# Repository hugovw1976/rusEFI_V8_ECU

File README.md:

# rusEFI_V8_ECU

- 8x 3A low-side drivers
- 4x 10A low_side drivers
- 8x 5v ignition or general purpose outputs (or 4 igniters/ 4general purpose otputs)
- One H-bridge for electronic throttle
- 10x Analog voltage inputs
- 4x Analog temperature (5v pullup) inputs
- 2x VR crank/cam/vehicle speed inputs
- 6x hall cam/crank or digital input (-2 if VR sensors used)
- Base on proteus board (intended for use with proteus firmware microcontroller, pin matched to correspond output)

rusEFI project: https://github.com/rusefi/rusefi
Proteus project: https://github.com/mck1117/proteus

Please do not use the gerber files, the board is not tested yet!
P&P file not tested on JLC PCB (Board is hand soldering)

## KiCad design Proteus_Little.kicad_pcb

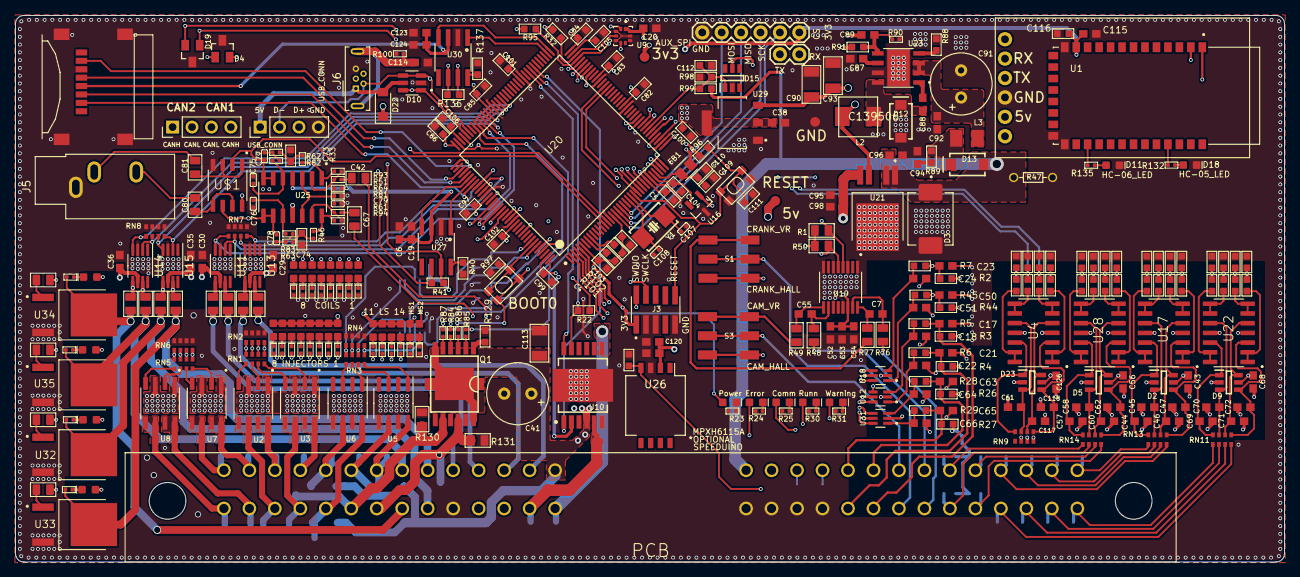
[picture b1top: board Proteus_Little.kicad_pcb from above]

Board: 4 copper layers, 166.0 x 71.5 mm, 394 parts (0 on the bottom side), 288 nets.

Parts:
C1, C2, C3, C8, C9, C10, C11, C12, C13, C14, C15, C16, C25, C26, C27, C28, C31, C32, C33, C34, C39, C40, C48, C49, C54, C87: 10nF; 0603
C4, C5, C82, C83, C84, C85, C86, C97, C99, C104, C109, C111: 10nf; C0603
C6, C53, C92, C95, C96, C119, C120, C123: 1.0uF; 0603
C7, C17, C18, C21, C22, C23, C24, C50, C51, C55, C63, C64, C65, C66: 1nF; 0603
C19, C20, C29, C30, C35, C36, C37, C44, C45, C46, C47, C52, C57, C58, C60, C61, C62, C69, C70, C71, C72, C88, C115, C117, C118, C124, C125: 100nF; 0603
C38, C94: 4.7uF; 0603
C41, C91: 56uF; E3,5-8
C42, C67: 3.3nf; C0805
C43, C56, C68, C126: 33nF; 0603
C73, C74: 680pf; C0603
C75, C76: 47PF; C0402
C77, C78: 330PF 50V; C0402
C79: 10nf; C0402
C80, C81: 10uf; C0805
C89: 270PF; 0603
C90, C93, C113: 10uf; C1206
C98: 22uf; 0603
C100, C101, C102, C103: 4.7uf; C0603
C105, C106: 2.2uf; C0603
C107, C108: 33pf; C0402
C110: 4.7uF; C0603
C112, C116: 1uf; C0603
C114: 100nf; 0603
D1: BLUE; LED-0603
D2, D5, D9, D15, D23: SRV05-4.TCT; SOT95P280X145-6N
D3: SM15T33CA; DIOM7959X262N
D4, D19: PESD1CAN; SOT23
D6, D7: GREEN; LED-0603
D8, D11, D18, D27, D28, D29, D30, D31, D32, D33, D34, D35, D36, D37, D38, D39, D40, D41, D42, D43, D44, D45, D46, D47, D48, D49, D50, D51, D52: RED; LED-0603
D10: USBLC6-2SC6; SOT95P280X145-6N
D12, D13: C8678; SMA-DIODE
D14: Yellow; LED-0603
D16, D17, D20, D21: MBR0520LT1G; SOD-123FL
D22: MBR0520LT1G; SODFL3718X115
FB1: FERRITE_BEAD; BEADC2012X105N
J1, J9: Conn_01x04_Female; PinHeader_1x04_P2.54mm_Vertical
J2: 47219-2001; MOLEX_47219-2001
J3: 62131021021
J4: CONN_06NO_SILK_NO_POP; 1X06_NO_SILK
J5: AudioJack3; Jack_3.5mm_CUI_SJ1-3533NG_Horizontal
J6: USB_B_Micro; USB_Micro-B_Wuerth_614105150721_Vertical
J7: CONN_02; 1X02
J8: CONN_06SILK_FEMALE_PTH; 1X06
L2: 10U; 0503
L3: 2.2U; L3225M
Q1: BTS5215L; PG-DSO-12-9
R1, R48, R49, R50, R76, R77: 10K; R0805
R2, R3, R4, R26, R27, R32, R44, R95: 2.2K; R0603
R5, R6, R7, R28, R29, R45: 3.3K; R0603
R8, R9, R10, R11, R12, R13, R14, R15: 100R; R0805
R16, R17, R34: 2.7K; R0603
R18, R19, R20, R21, R22, R40, R53, R54, R55, R56, R65, R67, R78, R79, R88, R96, R97, R98, R101, R102, R137, R138, R139, R140, R141, R147, R148, R149, R150: 10K; R0603
R23, R24, R25, R30, R31, R103, R104, R105, R106, R107, R108, R109, R110, R111, R112, R113, R114, R115, R116, R117, R118, R119, R120, R121, R122, R123, R124, R125, R126, R127, R128, R132, R135: 330R; R0402
R33, R46, R90: 12K; R0402
R35, R36, R37, R38, R57, R58, R59, R60, R68, R69, R70, R71, R143, R144, R145, R146: 5.6K; R0603
R39, R42, R43, R52, R66, R72, R73, R74, R75, R92, R133: 470K; R0603
R41, R136: 120R; R0603
R47: B72530T6170K062; R-5
R51, R61, R62, R63, R100: 100K; R0402
R64, R81: 22K; R0402
R80: 2.7k; R0603
R82, R83: 33K; R0402
R84, R85: 10K; R0402
R86, R87: 15K; R0402
R89: 1R; R0603
R91: 68K; R0603
R93, R94: 470K; R0402
R99: 82k; R0603
R129: 150R; R0603
R130, R131: 4.7K; R0805
R1020, R1021, R1022: 330R; R0805
R1023: 330r; R0805
RN1, RN2, RN3, RN4, RN5, RN6, RN7, RN8: 1K; 0603-ARC
RN9, RN11, RN13, RN14: 10K; 0603-ARC
S1, S3: JS202011SCQN; SW_JS202011SCQN
SW1, SW2: SPST_TACT-KMR2; KMR2
TP1, TP2, TP3: TEST-POINT3X5; PAD.03X.05
U1: HC-05; XCVR_HC-05
U2, U3, U7, U8: VNS3NV04DP-E; SOIC127P600X175-8N
U4, U17, U22, U25, U28: MCP6004-E_SL; SOIC127P600X175-14N
U5, U6: VNLD5090TR-E; SOIC-8_3.9x4.9mm_P1.27mm
U9: LPS25HBTR; PQFN60P250X250X80-10N
U10: TLE9201SG; SOP100P1030X260-13N
U11, U13, U14, U15: MIC4427; MSOP-8_3x3mm_P0.65mm
U12, U18, U31: 74HC2G17; SOP65P210X110-6N
U16: REF3033AIDBZR; SOT95P237X112-3N
U19: MAX9926UAEE+; SOP63P602X175-16N
U20: STM32F407ZGT6; STMICROELECTRONICS_STM32F429ZGT6_2
U21: TLE4251DATMA1; TO114P998X235-5
U23: LMR14020SDDAR; VREG_LM5017MR_NOPB
U26: MPXAZ6115A; Freescale_98ARH99066A
U27, U30: VD230; SO08
U29: AMS1117-3.3; SOT229P700X180-4N
U32, U33, U34, U35: ISL9V3040D3STV; TO229P990X238-4N
U36: 74HC125DB,112; SOP65P775X265-14N
U$1: MCP6002-E_SN; SOIC127P599X175-8N
U$3: 211PL562L0011; 211PL562L0011_2
Y1: CRYSTAL_NX5032GA; CRYSTAL_2-SMD-5X3

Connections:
+3V3: C4.1, C5.1, C6.1, C19.1, C20.1, C38.2, C82.1, C83.1, C84.1, C85.1, C86.1, C97.1, C99.1, C100.1, C101.1, C102.1, C103.1, C115.2, C116.1, C123.1, C124.1, D6.A, FB1.2, J2.4, J3.1, J8.6, R1.2, R22.2, R32.1, R50.2, R64.2, R86.1, R87.1, R95.2, R96.1, R101.2, R102.2, SW2.1, SW2.3, TP2.P$1, U1.12, U9.1, U9.6, U9.10, U10.2, U20.6, U20.17, U20.30, U20.39, U20.52, U20.62, U20.72, U20.84, U20.95, U20.108, U20.121, U20.131, U20.143, U20.144, U25.4, U27.3, U29.2, U29.4, U30.3
+5V: C29.1, C30.1, C35.1, C36.1, C43.1, C52.2, C53.1, C54.2, C56.1, C68.1, C89.2, C90.1, C93.1, C119.1, C120.1, C125.2, C126.1, D2.5, D5.5, D9.5, D15.5, D22.1, D23.5, D27.A, D28.A, D29.A, D30.A, D31.A, D32.A, D33.A, D34.A, D35.A, D36.A, D37.A, D38.A, D49.A, D50.A, D51.A, D52.A, J4.2, L2.P$2, R91.2, TP1.P$1, U4.4, U11.6, U12.5, U13.6, U14.6, U15.6, U16.1, U17.4, U18.5, U19.14, U21.4, U22.4, U26.2, U28.4, U29.3, U31.5, U36.14, U$1.8
/5V_SENSORS: C37.1, C95.2, C98.2, R2.1, R3.1, R4.2, R16.2, R17.2, R26.1, R27.2, R34.2, R44.1, R80.2, U21.5, U$3.P55
/12 VOLT DIVIDER/12V_DIVIDED: C112.2, D15.1, R98.2, R99.1, U20.43
/12V: C96.2, D3.1, D13.A, R47.1, R99.2, U21.1, U21.2, U$3.P56
/12V_MR: C41.+, C113.1, D16.C, D17.C, D20.C, D21.C, Q1.6, Q1.12, Q1.EXP, U10.4, U$3.P15
/ANALOG1: R72.2, RN11.8, U$3.P39
/ANALOG1/ANALOG1_MCU: R21.2, R68.2, U20.26
/ANALOG1/ANALOG2_MCU: R20.2, R69.2, U20.27
/ANALOG1/ANALOG3_MCU: R19.2, R70.2, U20.28
/ANALOG1/ANALOG4_MCU: R18.2, R71.2, U20.29
/ANALOG2: R73.2, RN11.7, U$3.P40
/ANALOG2/ANALOG5_MCU: R35.2, R56.2, U20.34
/ANALOG2/ANALOG6_MCU: R36.2, R55.2, U20.35
/ANALOG2/ANALOG7_MCU: R37.2, R54.2, U20.36
/ANALOG2/ANALOG8_MCU: R38.2, R53.2, U20.37
/ANALOG3: R74.2, RN11.6, U$3.P41
/ANALOG3/ANALOG9_MCU: R143.2, R150.2, U20.40
/ANALOG3/ANALOG10_MCU: R144.2, R149.2, U20.41
/ANALOG3/ANALOG11_MCU: R145.2, R148.2, U20.42
/ANALOG4: R75.2, RN11.5, U$3.P42
/ANALOG5: R39.2, RN13.8, U$3.P46
/ANALOG6: R42.2, RN13.7, U$3.P45
/ANALOG7: R43.2, RN13.6, U$3.P44
/ANALOG8: R52.2, RN13.5, U$3.P43
/ANALOG9: R66.2, RN9.8, U26.4
/ANALOG10: R92.2, RN9.7, U$3.P53
/ANALOG11: R133.2, RN9.6, U$3.P54
/ANALOG_T1: R17.1, RN14.5, U$3.P48
/ANALOG_T2: R16.1, RN14.6, U$3.P37
/ANALOG_T3: R80.1, RN14.7, U$3.P47
/ANALOG_T4: R34.1, RN14.8, U$3.P38
/ANALOG_T/ANALOG_T1_MCU: R60.2, R65.2, U20.44
/ANALOG_T/ANALOG_T2_MCU: R59.2, R67.2, U20.45
/ANALOG_T/ANALOG_T3_MCU: R58.2, R78.2, U20.46
/ANALOG_T/ANALOG_T4_MCU: R57.2, R79.2, U20.47
/AUX_SPI_CS: J8.5, U20.18
/AUX_SPI_MISO: J8.3, U20.20
/AUX_SPI_MOSI: J8.2, U20.21
/AUX_SPI_SCK: J8.4, U20.19
/BARO/BARO_SCL: R95.1, U9.2, U20.69
/BARO/BARO_SDA: R32.2, U9.4, U20.70
/CAM+: S3.2, S3.5, U$3.P50
/CAM-: R48.2, U$3.P49
/CAN1H: D4.2, J1.4, R41.2, U27.7
/CAN1L: D4.1, J1.3, R41.1, U27.6
/CAN2H: D19.2, J1.1, R136.2, U30.7
/CAN2L: D19.1, J1.2, R136.1, U30.6
/CAN/CAN1_RX: U20.114, U27.4
/CAN/CAN1_TX: U20.115, U27.1
/CAN/CAN2_RX: U20.73, U30.4
/CAN/CAN2_TX: U20.74, U30.1
/COIL1: C28.1, D42.A, R11.2, U$3.P17
/COIL2: C27.1, D43.A, R10.2, U$3.P16
/COIL3: C25.1, D44.A, R8.2, U$3.P18
/COIL4: C26.1, D45.A, R9.2, U$3.P19
/COIL5: C33.1, D46.A, R14.2, R125.2, U33.4, U$3.P20
/COIL6: C34.1, D47.A, R15.2, R126.2, U32.4, U$3.P9
/COIL7: C31.1, D48.A, R12.2, R127.2, U35.4, U$3.P21
/COIL8: C32.1, D41.A, R13.2, R128.2, U34.4, U$3.P8
/CRANK+: S1.2, S1.5, U$3.P35
/CRANK-: R76.2, U$3.P36
/ETB/DIR: U10.1, U20.79
/ETB/DIS: R22.1, U10.11, U20.80
/ETB/ETB_PWM: U10.12, U20.81
/HI_SIDE/HS1_MCU: R84.1, U20.101
/HI_SIDE/HS2_MCU: R85.1, U20.100
/HS1: C48.2, D39.A, Q1.8, R130.1, U$3.P6
/HS2: C49.2, D40.A, Q1.10, R131.1, U$3.P7
/IGNITION_1/IGN1: RN7.7, U13.4, U20.118
/IGNITION_1/IGN2: RN7.8, U13.2, U20.117
/IGNITION_1/IGN3: RN7.6, U11.2, U20.99
/IGNITION_1/IGN4: RN7.5, U11.4, U20.98
/IGNITION_2/IGN5: RN8.8, U15.2, U20.97
/IGNITION_2/IGN6: RN8.7, U15.4, U20.93
/IGNITION_2/IGN7: RN8.6, U14.2, U20.92
/IGNITION_2/IGN8: RN8.5, U14.4, U20.91
/IN1: C65.2, R27.1, R29.1, U$3.P52
/IN4: C21.2, R4.1, R6.1, U$3.P33
/IN5: C17.2, R3.2, R5.1, U$3.P34
/IN6: C63.2, R26.2, R28.1, U$3.P51
/INPUTS/CAM+HALL: C23.2, R2.2, R7.1, S3.1, S3.4
/INPUTS/CAM+VR: R49.2, S3.3, S3.6
/INPUTS/CAM_IN: C24.2, R7.2, U18.3
/INPUTS/CAM_VR_MCU: R50.1, U19.5, U20.59
/INPUTS/CRANK+HALL: C50.2, R44.2, R45.1, S1.1, S1.4
/INPUTS/CRANK+VR: R77.2, S1.3, S1.6
/INPUTS/CRANK_IN: C51.2, R45.2, U18.1
/INPUTS/CRANK_VR_MCU: R1.1, U19.4, U20.58
/INPUTS/IN1_IN: C66.1, R29.2, U31.1
/INPUTS/IN1_MCU: U20.96, U31.6
/INPUTS/IN2_MCU: U18.4, U20.64
/INPUTS/IN3_MCU: U18.6, U20.65
/INPUTS/IN4_IN: C22.1, R6.2, U12.1
/INPUTS/IN4_MCU: U12.6, U20.67
/INPUTS/IN5_IN: C18.2, R5.2, U12.3
/INPUTS/IN5_MCU: U12.4, U20.66
/INPUTS/IN6_IN: C64.2, R28.2, U31.3
/INPUTS/IN6_MCU: U20.68, U31.4
/KNOCK1: C42.1, U$3.P12
/KNOCK2: C67.1, U$3.P11
/KNOCK_/FILTERED1: C77.2, U20.14, U25.6, U25.7, U$1.2
/KNOCK_/FILTERED2: C78.1, U20.15, U25.8, U25.9, U$1.6
/LED1: D8.A, U20.2
/LED2: D1.A, U20.3
/LED3: D7.A, U20.4
/LED4: D14.A, U20.5
/LOW_SIDE_1/LS1_MCU: RN5.8, RN6.5, U20.123
/LOW_SIDE_1/LS2_MCU: RN5.7, RN6.6, U20.124
/LOW_SIDE_1/LS3_MCU: RN5.6, RN6.7, U20.125
/LOW_SIDE_1/LS4_MCU: RN5.5, RN6.8, U20.126
/LOW_SIDE_2/LS5_MCU: RN1.8, RN2.5, U20.127
/LOW_SIDE_2/LS6_MCU: RN1.7, RN2.6, U20.128
/LOW_SIDE_2/LS7_MCU: RN1.6, RN2.7, U20.129
/LOW_SIDE_2/LS8_MCU: RN1.5, RN2.8, U20.134
/LOW_SIDE_HIGH_CURRENT/LS11_BUFF: RN3.8, RN4.5, U36.11
/LOW_SIDE_HIGH_CURRENT/LS11_MCU: R138.1, U20.137, U36.12
/LOW_SIDE_HIGH_CURRENT/LS12_BUFF: RN3.7, RN4.6, U36.8
/LOW_SIDE_HIGH_CURRENT/LS12_MCU: R139.1, U20.139, U36.9
/LOW_SIDE_HIGH_CURRENT/LS13_BUFF: RN3.6, RN4.7, U36.6
/LOW_SIDE_HIGH_CURRENT/LS13_MCU: R140.1, U20.140, U36.5
/LOW_SIDE_HIGH_CURRENT/LS14_BUFF: RN3.5, RN4.8, U36.3
/LOW_SIDE_HIGH_CURRENT/LS14_MCU: R141.1, U20.141, U36.2
/LS1: C13.1, R103.2, U8.5, U8.6, U$3.P1
/LS2: C14.1, R104.2, U8.7, U8.8, U$3.P2
/LS3: C16.1, R105.2, U7.5, U7.6, U$3.P28
/LS4: C15.1, R106.2, U7.7, U7.8, U$3.P27
/LS5: C8.1, R107.2, U2.5, U2.6, U$3.P3
/LS6: C3.1, R108.2, U2.7, U2.8, U$3.P26
/LS7: C1.1, R109.2, U3.5, U3.6, U$3.P4
/LS8: C2.1, R110.2, U3.7, U3.8, U$3.P25
/LS11: C9.1, D21.A, R111.2, U6.6, U$3.P24
/LS12: C10.1, D20.A, R112.2, U6.8, U$3.P5
/LS13: C12.1, D17.A, R113.2, U5.6, U$3.P23
/LS14: C11.1, D16.A, R114.2, U5.8, U$3.P22
/MCU/D+: D10.1, D10.6, J6.3, J9.3, U20.104
/MCU/D-: D10.3, D10.4, J6.2, J9.2, U20.103
/MCU/SD_CS: J2.2, U20.116
/MCU/SD_MISO: J2.7, U20.112
/MCU/SD_MOSI: J2.3, U20.113
/MCU/SD_SCK: J2.5, U20.111
/OUT+: C39.2, U10.5, U$3.P13
/OUT-: C40.1, U10.7, U$3.P14
/RESET: C111.1, J3.10, R96.2, SW1.1, SW1.3, U20.25
/SWCLK: J3.4, U20.109
/SWDIO: J3.2, U20.105
/UART_RX: J4.5, J7.2, U1.2, U20.119
/UART_TX: J4.4, J7.1, U1.1, U20.122
/USB/SHIELD: C114.1, J6.6, R100.2
GND: C1.2, C2.2, C3.2, C4.2, C5.2, C6.2, C8.2, C9.2, C10.2, C11.2, C12.2, C13.2, C14.2, C15.2, C16.2, C17.1, C18.1, C19.2, C20.2, C21.1, C22.2, C23.1, C24.1, C25.2, C26.2, C27.2, C28.2, C29.2, C30.2, C31.2, C32.2, C33.2, C34.2, C35.2, C36.2, C37.2, C38.1, C39.1, C40.2, C41.-, C43.2, C44.2, C45.2, C46.2, C47.2, C48.1, C49.1, C50.1, C51.1, C52.1, C53.2, C54.1, C56.2, C57.2, C58.2, C60.2, C61.2, C62.2, C63.1, C64.1, C65.1, C66.2, C68.2, C69.2, C70.2, C71.2, C72.2, C73.2, C74.1, C75.2, C76.1, C79.2, C82.2, C83.2, C84.2, C85.2, C86.2, C87.2, C90.2, C91.-, C92.2, C93.2, C94.2, C95.1, C96.1, C97.2, C98.1, C99.2, C100.2, C101.2, C102.2, C103.2, C105.1, C106.1, C107.2, C108.2, C109.1, C110.1, C111.2, C112.1, C113.2, C114.2, C115.1, C116.2, C117.2, C118.2, C119.2, C120.2, C123.2, C124.2, C125.1, C126.2, D2.2, D3.2, D4.3, D5.2, D9.2, D10.2, D11.C, D12.A, D15.2, D18.C, D19.3, D23.2, J2.6, J2.G1, J2.G2, J2.G3, J2.G4, J3.3, J3.5, J3.9, J4.3, J5.S, J6.5, J8.1, J9.4, R18.1, R19.1, R20.1, R21.1, R23.2, R24.2, R25.2, R30.2, R31.2, R39.1, R40.1, R42.1, R43.1, R47.2, R52.1, R53.1, R54.1, R55.1, R56.1, R65.1, R66.1, R67.1, R72.1, R73.1, R74.1, R75.1, R78.1, R79.1, R81.1, R88.1, R90.2, R92.1, R97.1, R98.1, R100.1, R115.2, R116.2, R117.2, R118.2, R119.2, R120.2, R121.2, R122.2, R123.2, R124.2, R129.1, R130.2, R131.2, R133.1, R137.1, R138.2, R139.2, R140.2, R141.2, R147.1, R148.1, R149.1, R150.1, RN2.1, RN2.2, RN2.3, RN2.4, RN4.1, RN4.2, RN4.3, RN4.4, RN6.1, RN6.2, RN6.3, RN6.4, RN7.1, RN7.2, RN7.3, RN7.4, RN8.1, RN8.2, RN8.3, RN8.4, SW1.2, SW1.4, TP3.P$1, U1.13, U1.21, U1.22, U2.1, U2.3, U3.1, U3.3, U4.11, U5.5, U5.7, U6.5, U6.7, U7.1, U7.3, U8.1, U8.3, U9.3, U9.5, U9.8, U9.9, U10.6, U10.13, U11.3, U12.2, U13.3, U14.3, U15.3, U16.3, U17.11, U18.2, U19.1, U19.3, U19.6, U19.8, U19.11, U19.13, U20.16, U20.31, U20.38, U20.48, U20.51, U20.61, U20.83, U20.94, U20.107, U20.120, U20.130, U21.3, U22.11, U23.7, U23.9, U25.11, U26.3, U27.2, U28.11, U29.1, U30.2, U31.2, U32.3, U33.3, U34.3, U35.3, U36.1, U36.4, U36.7, U36.10, U36.13, U$1.4, U$3.P10, U$3.P29, U$3.P30, U$3.P31, U$3.P32
unnamed: C7.1, R77.1, U19.16
unnamed: C7.2, R76.1, U19.15
unnamed: C42.2, R51.1
unnamed: C44.1, D2.1, RN13.4, U17.12
unnamed: C45.1, D2.3, RN13.3, U17.10
unnamed: C46.1, D2.6, RN13.2, U17.5
unnamed: C47.1, D2.4, RN13.1, U17.3
unnamed: C55.1, R49.1, U19.9
unnamed: C55.2, R48.1, U19.10
unnamed: C57.1, D5.1, RN14.4, U28.12
unnamed: C58.1, D5.3, RN14.3, U28.10
unnamed: C60.1, D5.6, RN14.2, U28.5
unnamed: C61.1, D23.3, RN9.3, U4.10
unnamed: C62.1, D5.4, RN14.1, U28.3
unnamed: C67.2, R61.1
unnamed: C69.1, D9.1, RN11.4, U22.12
unnamed: C70.1, D9.3, RN11.3, U22.10
unnamed: C71.1, D9.6, RN11.2, U22.5
unnamed: C72.1, D9.4, RN11.1, U22.3
unnamed: C73.1, R33.2, R62.1
unnamed: C74.2, R46.2, R63.1
unnamed: C75.1, R82.2, U25.5
unnamed: C76.2, R83.2, U25.10
unnamed: C77.1, R62.2, R82.1
unnamed: C78.2, R63.2, R83.1
unnamed: C79.1, R64.1, R81.2, U25.3, U25.12
unnamed: C80.1, U$1.5, U$1.7
unnamed: C80.2, J5.R
unnamed: C81.1, U$1.1, U$1.3
unnamed: C81.2, J5.T
unnamed: C87.1, U23.6
unnamed: C88.1, U23.1
unnamed: C88.2, D12.C, L2.P$1, U23.8
unnamed: C89.1, R90.1, R91.1, U23.5
unnamed: C91.+, C92.1, L3.2, U23.2, U23.3
unnamed: C94.1, R89.2
unnamed: C104.2, U16.2, U20.32
unnamed: C105.2, U20.71
unnamed: C106.2, U20.106
unnamed: C107.1, U20.24, Y1.1
unnamed: C108.1, U20.23, Y1.2
unnamed: C109.2, C110.2, FB1.1, U20.33
unnamed: C117.1, D23.6, RN9.2, U4.5
unnamed: C118.1, D23.4, RN9.1, U4.3
unnamed: D1.C, R25.1
unnamed: D6.C, R23.1
unnamed: D7.C, R30.1
unnamed: D8.C, R24.1
unnamed: D10.5, D22.2, J6.1, J9.1
unnamed: D11.A, R135.2
unnamed: D13.C, L3.1, R89.1
unnamed: D14.C, R31.1
unnamed: D18.A, R132.2
unnamed: D23.1, RN9.4, U4.12
unnamed: D27.C, R103.1
unnamed: D28.C, R104.1
unnamed: D29.C, R105.1
unnamed: D30.C, R106.1
unnamed: D31.C, R107.1
unnamed: D32.C, R108.1
unnamed: D33.C, R109.1
unnamed: D34.C, R110.1
unnamed: D35.C, R111.1
unnamed: D36.C, R112.1
unnamed: D37.C, R113.1
unnamed: D38.C, R114.1
unnamed: D39.C, R115.1
unnamed: D40.C, R116.1
unnamed: D41.C, R117.1
unnamed: D42.C, R118.1
unnamed: D43.C, R119.1
unnamed: D44.C, R120.1
unnamed: D45.C, R121.1
unnamed: D46.C, R122.1
unnamed: D47.C, R123.1
unnamed: D48.C, R124.1
unnamed: D49.C, R125.1
unnamed: D50.C, R126.1
unnamed: D51.C, R127.1
unnamed: D52.C, R128.1
unnamed: Q1.1, R129.2
unnamed: Q1.2, R85.2
unnamed: Q1.3, R86.2
unnamed: Q1.4, R84.2
unnamed: Q1.5, R87.2
unnamed: R8.1, U11.7
unnamed: R9.1, U11.5
unnamed: R10.1, U13.7
unnamed: R11.1, U13.5
unnamed: R33.1, R93.2, U25.1
unnamed: R35.1, U17.1, U17.2
unnamed: R36.1, U17.6, U17.7
unnamed: R37.1, U17.8, U17.9
unnamed: R38.1, U17.13, U17.14
unnamed: R40.2, U27.8
unnamed: R46.1, R94.2, U25.14
unnamed: R51.2, R93.1, U25.2
unnamed: R57.1, U28.1, U28.2
unnamed: R58.1, U28.6, U28.7
unnamed: R59.1, U28.8, U28.9
unnamed: R60.1, U28.13, U28.14
unnamed: R61.2, R94.1, U25.13
unnamed: R68.1, U22.1, U22.2
unnamed: R69.1, U22.6, U22.7
unnamed: R70.1, U22.8, U22.9
unnamed: R71.1, U22.13, U22.14
unnamed: R88.2, U23.4
unnamed: R97.2, SW2.2, SW2.4, U20.138
unnamed: R101.1, U20.8
unnamed: R102.1, U20.9
unnamed: R132.1, U1.31
unnamed: R135.1, U1.24
unnamed: R137.2, U30.8
unnamed: R143.1, U4.1, U4.2
unnamed: R144.1, U4.6, U4.7
unnamed: R145.1, U4.8, U4.9
unnamed: R146.1, U4.13, U4.14
unnamed: R146.2, R147.2
unnamed: R1020.1, U32.1
unnamed: R15.1, R1020.2, U15.5
unnamed: R14.1, R1021.1, U15.7
unnamed: R1021.2, U33.1
unnamed: R1022.1, U34.1
unnamed: R13.1, R1022.2, U14.5
unnamed: R1023.1, U35.1
unnamed: R12.1, R1023.2, U14.7
unnamed: RN1.1, U2.4
unnamed: RN1.2, U2.2
unnamed: RN1.3, U3.4
unnamed: RN1.4, U3.2
unnamed: RN3.1, U6.3
unnamed: RN3.2, U6.1
unnamed: RN3.3, U5.3
unnamed: RN3.4, U5.1
unnamed: RN5.1, U8.4
unnamed: RN5.2, U8.2
unnamed: RN5.3, U7.4
unnamed: RN5.4, U7.2

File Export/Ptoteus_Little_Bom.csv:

Qty,Value,Device,Package,LCSC PART #,MOUSER PART #,Parts
1,B72530T6170K062,VARISTOR-5,R-5,C693526,,R47
5,100K,SMD-RES-100K-1%-1/16W(0402),R0402,C25741,,"R51, R61, R62, R63, R100"
8,100R,SMD-RES-100R-5%-1/8W(0805),R0805,C441975,,"R8, R9, R10, R11, R12, R13, R14, R15"
4,10K,4R-N0603-ARC,0603-ARC,C29718,,"RN9, RN11, RN13, RN14"
2,10K,SMD-RES-10K-1%-1/16W(0402),R0402,C25744,,"R84, R85"
29,10K,SMD-RES-10K-1%-1/10W(0603),R0603,C323556,,"R18, R19, R20, R21, R22, R40, R53, R54, R55, R56, R65, R67, R78, R79, R88, R96, R97, R98, R101, R102, R137, R138, R139, R140, R141, R147, R148, R149, R150"
6,10K,SMD-RES-10K-1%-1/4W(0805),R0805,C161788,,"R1, R48, R49, R50, R76, R77"
2,15K,SMD-RES-15K-1%-1/16W(0402),R0402,C25756,,"R86, R87"
1,150R,SMD-RES-150-1%-1/4W(0805),R0805,C365244,,R129
2,4.7K,SMD-RES-4.7K-1%-1/4W(0805),R0805,C363267,,"R130,R131"
2,120R,SMD-RES-120R-5%-1/10W(0603),R0603,C22787,,"R41, R136"
8,1K,4R-N0603-ARC,0603-ARC,C20197,,"RN1, RN2, RN3, RN4, RN5, RN6, RN7, RN8"
3,12K,SMD-RES-12K-1%-1/16W(0402),R0402,C102781,,"R33, R46, R90"
1,1R,SMD-RES-1R-5%-1/10W(0603),R0603,C22936,,R89
8,2.2K,SMD-RES-2.2K-5%-1/10W(0603),R0603,C4190,,"R2, R3, R4, R26, R27, R32, R44, R95"
4,2.7K,SMD-RES-2.7K-1%-1/10W(0603),R0603,C328353,,"R16, R17, R34, R80"
2,22K,SMD-RES-22R-1%-1/16W(0402),R0402,C25768,,"R64, R81"
6,3.3K,SMD-RES-3.3K-1%-1/10W(0603),R0603,C22978,,"R5, R6, R7, R28, R29, R45"
33,330R,SMD-RES-330R-1%-1/16W(0402),R0402,C328315,,"R23, R24, R25, R30, R31, R103, R104, R105, R106, R107, R108, R109, R110, R111, R112, R113, R114, R115, R116, R117, R118, R119, R120, R121, R122, R123, R124, R125, R126, R127, R128, R132, R135"
4,330R,SMD-RES-330R-1%-1/8W(0805),R0805,C441945,,"R1020, R1021, R1022, R1023"
2,33K,SMD-RES-33K-1%-1/16W(0402),R0402,C25779,,"R82, R83"
11,470K,SMD-RES-470K-1%-1/10W(0603),R0603,C23178,,"R39, R42, R43, R52, R66, R72, R73, R74, R75, R92, R133"
2,470K,SMD-RES-470K-1%-1/16W(0402),R0402,C25790,,"R93, R94"
16,5.6K,SMD-RES-5.6K-1%-1/10W(0603),R0603,C114627,,"R35, R36, R37, R38, R57, R58, R59, R60, R68, R69, R70, R71, R143, R144, R145, R146"
1,68K,SMD-RES-68K-1%-1/10W(0603),R0603,C23231,,R91
1,82k,SMD-RES-82K-1%-1/10W(0603),R0603,C23254,,R99
8,1.0uF,1uF ±10% 50V X7R 0603,C0603,C525334,,"C6, C53, C92, C95, C96, C112, C116, C119, C120, C123"
28,100nF,100nF ±10% 50V X7R 0603,C0603,C14663,,"C19, C20, C29, C30, C35, C36, C37, C44, C45, C46, C47, C52,  C57, C58, C60,  C61, C62, C69, C70, C71, C72, C88, C114, C115, C117, C118, C124, C125"
38,10nF,10nF ±10% 50V X7R 0603,C0603,C57112,,"C1, C2, C3, C4, C5 C8, C9, C10, C11, C12, C13, C14, C15, C16, C25, C26, C27, C28, C31, C32, C33, C34, C39, C40, C48, C49, C54, C82, C83, C84, C85, C86,C87, C97, C99, C104, C109, C111"
1,10nf,CERAMIC-10NF-50V-10%-X7R(0402),C0402,C15195,,C79
2,10uf,10uF ±10% 16V X7R 0805,C0805,C95841,,"C80, C81"
3,10uf,10uF ±10% 25V X7R 1206,C1206,C14860,,"C90, C93, C113"
14,1nF,1nF ±10% 50V X7R 0603,C0603,C1588,,"C7, C17, C18, C21, C22, C23, C24, C50, C51, C55, C63, C64, C65, C66"
2,2.2uf,2.2uF ±10% 25V X7R 0603,C0603,C99228,,"C105, C106"
1,22uf,22uF ±20% 10V X5R 0603,C0603,C84419,,C98
1,270PF,270pF ±10% 50V X7R 0603,C0603,C1608,,C89
2,3.3nf,3.3nF ±10% 50V X7R 0805,C0805,C53175,,"C42, C67"
2,330PF 50V,330pF ±5% 50V C0G 0402,C0402,C1535,,"C77, C78"
4,33nF,33nF ±10% 50V X7R 0603,C0603,C21117,,"C43, C56, C68, C118"
2,33pf,33pF ±5% 50V C0G 0402,C0402,C1562,,"C107, C108"
7,4.7uF,4.7uF ±10% 35V X5R 0603,C0603,C329940,,"C38, C94, C100, C101, C102, C103, C110"
2,47PF,47pF ±5% 50V C0G 0402,C0402,C1567,,"C75, C76"
2,680pf,680pF ±10% 50V X7R 0603,C0603,C1630,,"C73, C74"
2,56uF,CPOL-USE3.5-8,"E3,5-8",,667-EEH-AZF1H560,"C41, C91"
1,10U,"10uH ±20% 3.2A 125mΩ SMD,5.2x5.4x3.0mm",0503,C139506,,L2
1,2.2U,2.2uH ±5% 320mA 1Ω 1210 Inductors,1210,C36828,,L3
3,74HC2G17,Dual non-inverting Schmitt trigger,SOT-363_SC-70-6,C94189,,"U12, U18, U31"
1,AMS1117-3.3,AMS1117-3.3,SOT-223,C6186,,U29
2,SMA_DIODE,Schottky Barrier Diodes 40V 3A 500mV @ 3A,SMA(DO-214AC),C85098,,"D12, D13"
4,DSS34,DIODE_SOD-123FL,SOD-123FL,C511866,,"D16, D17, D20, D21"
1,B5819W,Schottky Barrier Diodes,SOD-123FL,C8598,,D22
2,PESD1CAN,PESD1CAN,SOT23,C343993,,"D4, D11"
1,SM15T33CA,BIDIRECTIONAL TVS,SMC(DO-214AB),C133707,,D3
5,SRV05-4.TCT,SRV05-4.TCT,SOT-23-6,C85364,,"D2, D5, D9, D15, D23"
1,USBLC6-2SC6,SOT-23-6 Diodes,SOT-23-6,C7519,,D10
1,Yellow,LED-YELLOW0603,LED-0603,C84268,,D14
29,Blue,LED-BLUE0603,LED-0603,C72041,,"D8, D11, D18, D27, D28, D29, D30, D31, D32, D33, D34, D35, D36, D37, D38, D39, D40, D41, D42, D43, D44, D45, D46, D47, D48, D49, D50, D51, D52"
1,Red,LED-RED0603,LED-0603,C72044,,D1
2,Green,LED-GREEN0603,LED-0603,C72043,,"D6, D7"
2,K3-2235S-F1,DPDT On-On SMD Toggle Switches,SW_JS202011SCQN,C223858,,"S1, S3"
2,KMR221GLFS,SPST_SMD Tactile Switches,SMD 4.6x2.8,C72443,,"SW1, SW2"
4,ISL9V3040D3ST,Ignition IGBT,TO-252AA,C462128,,"U32, U33, U34, U35"
1,LMR14020SDDAR,40V 2A DC-DC Converters,SO PowerPAD-8,C187824,,U23
1,LPS25HBTR,Pressure Sensors,HLGA-10L,C87898,,U9
1,MAX9926UAEE/V+,Sensor Interface ICs,QSOP-16,C2678421,,U19
1,MCP6002T-E/MS,Low Power OpAmps,SOIC-8_150mil,C7377,,U$1
5,MCP6004T,Low Power OpAmps,SOIC-14,C7378,,"U17, U22, U25, U28"
4,MIC4427YMM-TR,MIC4427YMM-TR,MSOP-8,C144222,,"U11, U13, U14, U15"
1,REF3033AIDBZR,Voltage References,SOT-23(SOT-23-3),C36658,,U16
1,STMICROELECTRONICS,STM32F429ZGT6,LQFP-144_20x20x05P,C46525,,U20
1,TLE4251DATMA1,LDO Voltage Regulators,TO252-5,C539669,,U21
1,IFX9201SGAUMA1,6 A H-Bridge with SPI,SO-12,C112633,,U10
2,SN65HVD230DR,Transceiver CAN 1/1 1Mbps,SOIC-8_150mil,C12084,,"U27, U30"
1,BTS5215L,MOSFET Gate Drivers,PG-DSO-12,C386329,,Q1
4,VNS3NV04PTR-E,MOSFET Gate Drivers,SO-8,C146561,,"U2, U3, U5, U6, U7, U8"
1,8MHz ±10ppm 20pF 60Ω,SMD Crystal Resonators,SMD-5032_2P,C115962,,Y1
1,FERRITE_BEAD,Ferrite Beads,F0805,C1015,,FB1
1,USB_CONN,U-D-M5DD-W-1,,C145795,,J6
1,MPXH6115A,Pressure Sensor,SSOP-8,ONLY FOR SPEEDUINO,841-MPXH6115A6U,PS1
1,SD_CONNECTOR,Connector microSD™ Memory Card 8 SMD,,C125814,,J2
1,AUDIO JACK 3.5MM,CUI DEVICES 3.5MM AUDIO JACK NO SWITCH,,,490-SJ1-3533NG,J5
1,"74HC125DB,112",Quadruple Bus Buffer Gates,SSOP-14,C507233,,U36
2,VNLD5090TR-E,Low-side driver,SO-8,C222209,,"U5, U6"

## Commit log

2021-08-17 R42_Ecu
    Engine Management for Audi V8 ABZ
